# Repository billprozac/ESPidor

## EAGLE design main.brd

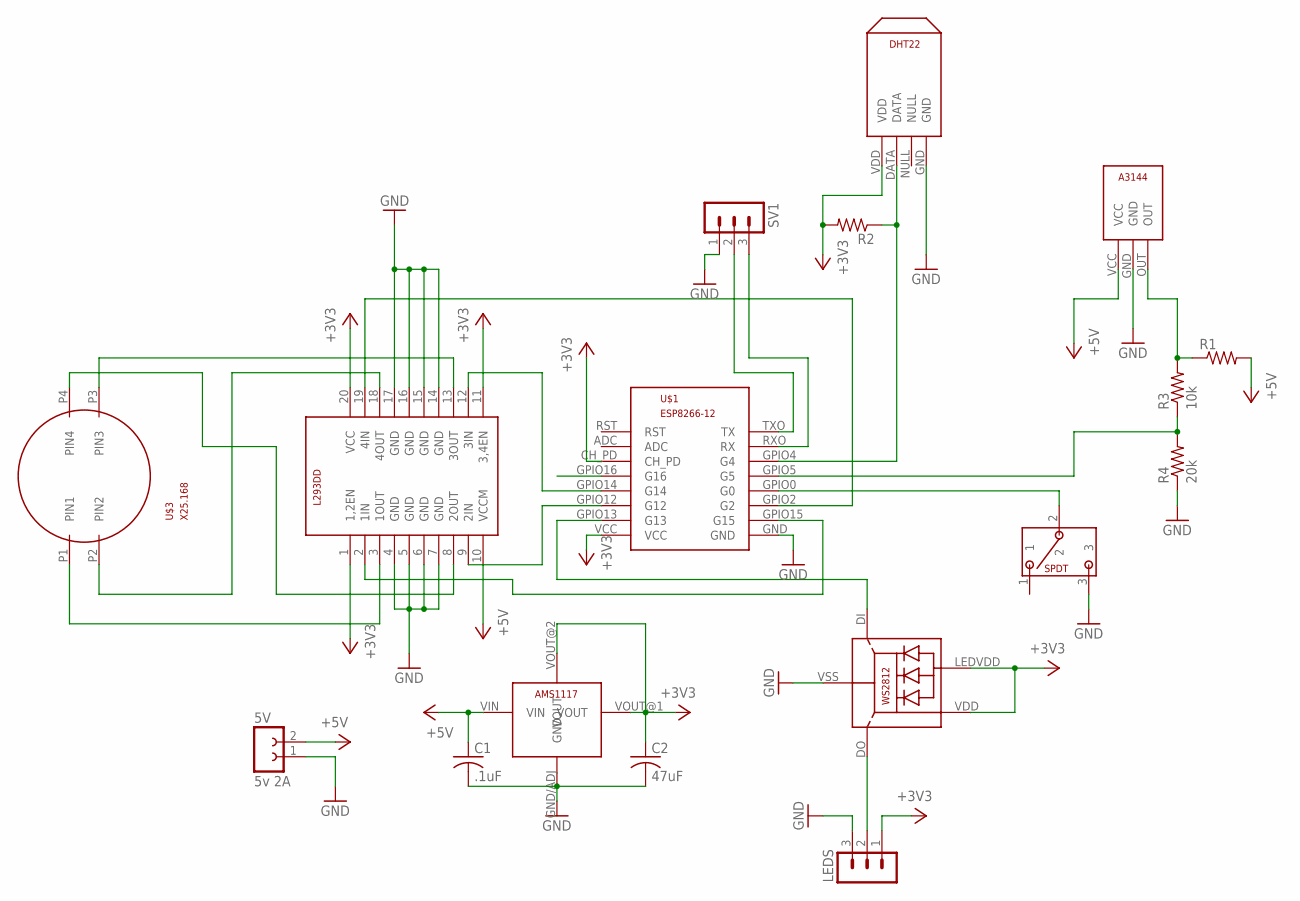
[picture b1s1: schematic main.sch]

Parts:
5V: 5v 2A; FE02-1
C1: .1uF; C0805
C2: 47uF; C0805
LED1: WS2812
LEDS: MA03-1
R1, R2: R-US_R0805; R0805
R3: 10k; R0805
R4: 20k; R0805
SV1: MA03-1
U$1: ESP12ESP12; ESP12
U$3: X25.168X25.SMT; X25-SMT
U$4: A3144
U$5: DH22FLAT
U$6: AMS11173.3V; AMS1117
U$7: SMT-SPDT; SPDT
U$8: L293DD; SO20

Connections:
+3V3: C2.1, LED1.LEDVDD, LED1.VDD, LEDS.1, R2.2, U$1.CH_PD, U$1.VCC, U$5.VDD, U$6.VOUT@1 (VOUT), U$6.VOUT@2 (VOUT), U$8.1 (1,2EN), U$8.11 (3,4EN), U$8.20 (VCC)
+5V: 5V.2, C1.1, R1.2, U$4.VCC, U$6.VIN, U$8.10 (VCCM)
GND: 5V.1, C1.2, C2.2, LED1.VSS (GND), LEDS.3, R4.1, SV1.1, U$1.GND, U$4.GND, U$5.GND, U$6.GND/ADJ (GND), U$7.3, U$8.4 (GND), U$8.5 (GND), U$8.6 (GND), U$8.7 (GND), U$8.14 (GND), U$8.15 (GND), U$8.16 (GND), U$8.17 (GND)
unnamed: U$3.P1 (PIN1), U$8.3 (1OUT)
unnamed: U$1.GPIO15 (G15), U$8.2 (1IN)
unnamed: R1.1, R3.2, U$4.OUT
unnamed: U$3.P4 (PIN4), U$8.8 (2OUT)
unnamed: R2.1, U$1.GPIO4 (G4), U$5.DATA
unnamed: LED1.DO, LEDS.2
unnamed: U$3.P3 (PIN3), U$8.13 (3OUT)
unnamed: SV1.3, U$1.RXO (RX)
unnamed: SV1.2, U$1.TXO (TX)
unnamed: R3.1, R4.2, U$1.GPIO5 (G5)
unnamed: LED1.DI, U$1.GPIO13 (G13)
unnamed: U$1.GPIO12 (G12), U$8.9 (2IN)
unnamed: U$1.GPIO14 (G14), U$8.12 (3IN)
unnamed: U$1.GPIO2 (G2), U$8.19 (4IN)
unnamed: U$1.GPIO0 (G0), U$7.2
unnamed: U$3.P2 (PIN2), U$8.18 (4OUT)

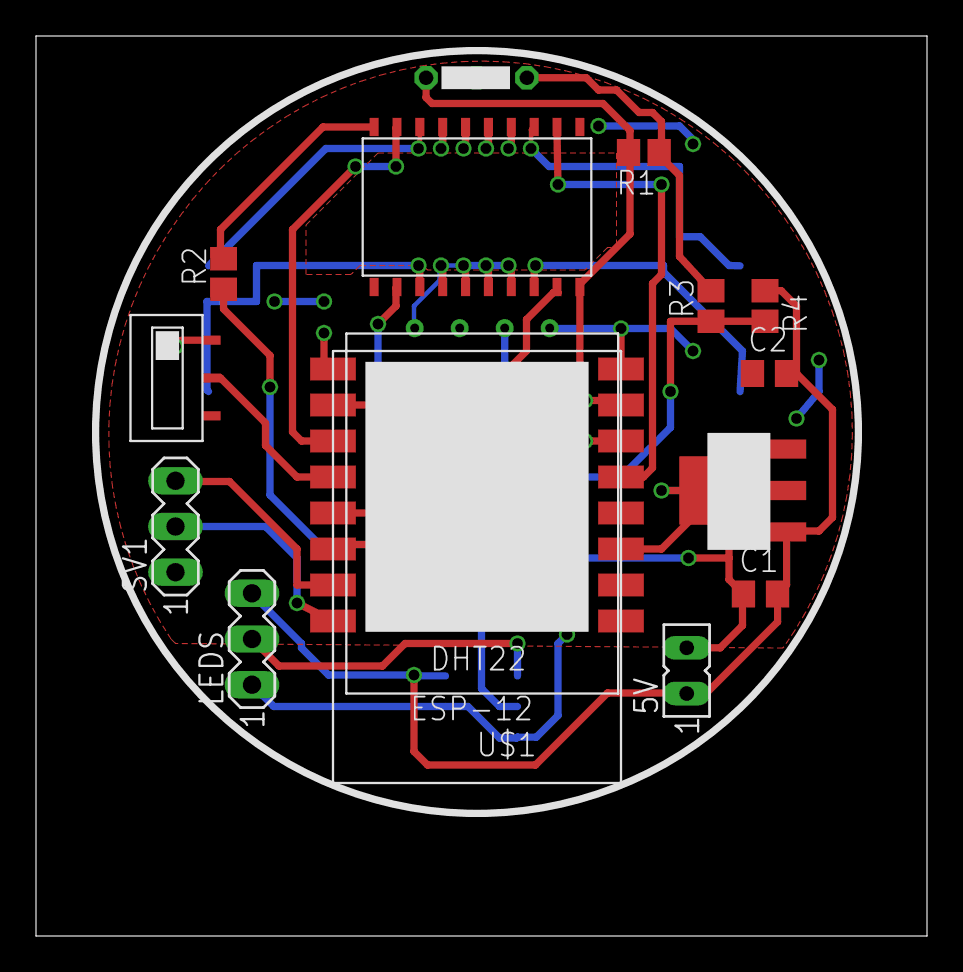
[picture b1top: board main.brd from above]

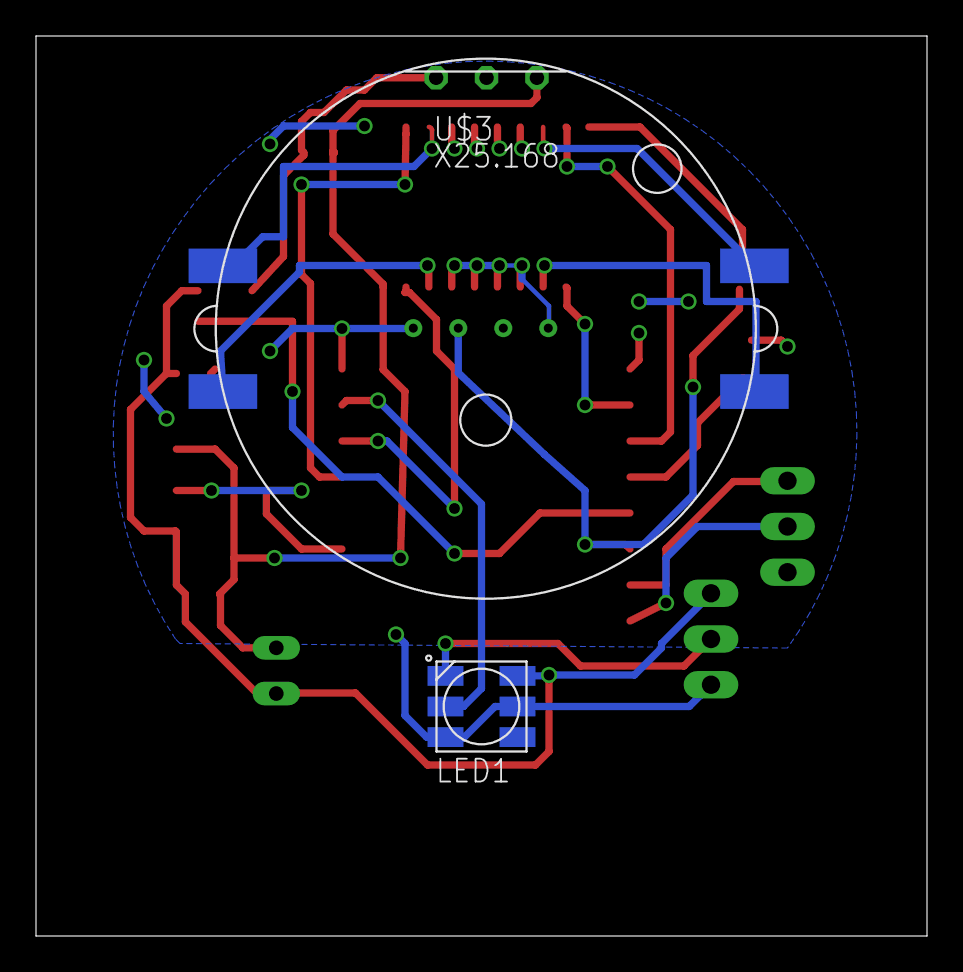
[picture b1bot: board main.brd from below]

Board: 2 copper layers, 49.5 x 50.0 mm, 17 parts (2 on the bottom side), 19 nets.

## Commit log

2015-02-18 :confetti_ball: Added .gitattributes
2015-02-18 Added base files
